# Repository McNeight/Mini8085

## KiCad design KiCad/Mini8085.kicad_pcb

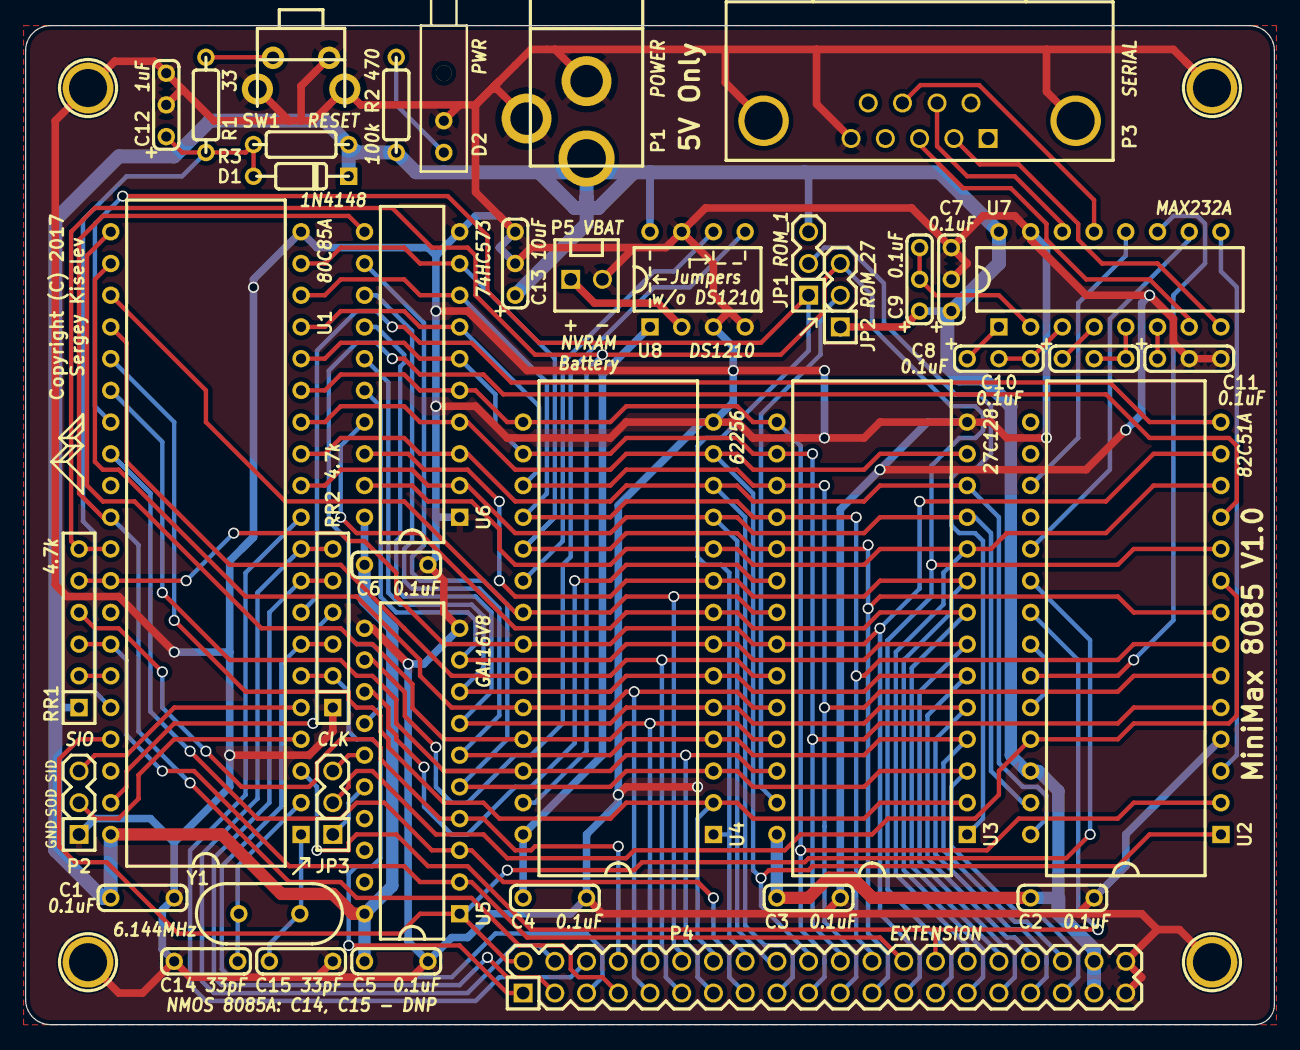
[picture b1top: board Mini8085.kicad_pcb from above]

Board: 2 copper layers, 100.0 x 80.0 mm, 44 parts (0 on the bottom side), 74 nets.

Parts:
C1, C2, C3, C4, C5, C6: 0.1uF; Cap_Cer_508
C7, C8, C9, C10, C11: 0.1uF; Cap_Pol_508_3
C12: 1uF; Cap_Pol_508_3
C13: 10uF; Cap_Pol_508_3
C14, C15: 33pF; Cap_Cer_508
D1: 1N4148; Diode_762
D2: PWR; LED_Dialight_566-0206F
HOLE1, HOLE2, HOLE3, HOLE4: CONN_1; Hole_3mm
JP1: ROM_1; Conn_Pin_Header_3x1_2.54mm
JP2: ROM_27; Conn_Pin_Header_3x1_2.54mm
JP3: CLK; Conn_Pin_Header_3x1_2.54mm
P1: POWER; Conn_Power_Jack_Circular_Pads
P2: SIO; Conn_Pin_Header_3x1_2.54mm
P3: SERIAL; Conn_Dsub_DE9M
P4: EXTENSION; Conn_Pin_Header_20x2_2.54mm
P5: VBAT; Conn_Friction_Lock_2P_2.54mm
R1: 33; Res_762
R2: 470; Res_762
R3: 100k; Res_762
RR1, RR2: 4.7k; Conn_SIL6
SW1: RESET; Switch_Tactile_6mm_Right
U1: 80C85A; IC_DIP40_600
U2: 82C51A; IC_DIP28_600
U3: 27C128; IC_DIP28_600
U4: 62256; IC_DIP28_600
U5: GAL16V8; IC_DIP20_300
U6: 74HC573; IC_DIP20_300
U7: MAX232A; IC_DIP16_300
U8: DS1210; IC_DIP8_300
Y1: 6.144MHz; Crystal_HC-49U_Vert

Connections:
/3.072MHz: P4.2, U1.37 (CLK), U2.20 (CLK), U5.1 (I/CLK)
/153.6kHz: JP3.3, U5.15 (I/O5)
/307.2kHz: JP3.1, U5.16 (I/O4)
/A0: P4.30, U2.12 (C/~D), U3.10 (A0), U4.10 (A0), U6.19 (O0)
/A1: P4.29, U3.9 (A1), U4.9 (A1), U6.18 (O1)
/A2: P4.32, U3.8 (A2), U4.8 (A2), U6.17 (O2)
/A3: P4.31, U3.7 (A3), U4.7 (A3), U5.9 (I8), U6.16 (O3)
/A4: P4.34, U3.6 (A4), U4.6 (A4), U5.8 (I7), U6.15 (O4)
/A5: P4.33, U3.5 (A5), U4.5 (A5), U5.7 (I6), U6.14 (O5)
/A6: P4.36, U3.4 (A6), U4.4 (A6), U5.6 (I5), U6.13 (O6)
/A7: P4.35, U3.3 (A7), U4.3 (A7), U5.5 (I4), U6.12 (O7)
/A8: P4.10, U1.21 (A8), U3.25 (A8), U4.25 (A8)
/A9: P4.9, U1.22 (A9), U3.24 (A9), U4.24 (A9)
/A10: P4.12, U1.23 (A10), U3.21 (A10), U4.21 (A10)
/A11: P4.11, U1.24 (A11), U3.23 (A11), U4.23 (A11)
/A12: P4.14, U1.25 (A12), U3.2 (A12), U4.2 (A12)
/A13: P4.13, U1.26 (A13), U3.26 (A13), U4.26 (A13)
/A14: JP1.1, P4.16, U1.27 (A14), U4.1 (A14)
/A15: P4.15, U1.28 (A15), U5.3 (I2)
/AD0: P4.18, U1.12 (AD0), U2.27 (D0), U3.11 (DQ0), U4.11 (DQ0), U6.2 (D0)
/AD1: P4.17, U1.13 (AD1), U2.28 (D1), U3.12 (DQ1), U4.12 (DQ1), U6.3 (D1)
/AD2: P4.20, U1.14 (AD2), U2.1 (D2), U3.13 (DQ2), U4.13 (DQ2), U6.4 (D2)
/AD3: P4.19, U1.15 (AD3), U2.2 (D3), U3.15 (DQ3), U4.15 (DQ3), U6.5 (D3)
/AD4: P4.22, U1.16 (AD4), U2.5 (D4), U3.16 (DQ4), U4.16 (DQ4), U6.6 (D4)
/AD5: P4.21, U1.17 (AD5), U2.6 (D5), U3.17 (DQ5), U4.17 (DQ5), U6.7 (D5)
/AD6: P4.24, U1.18 (AD6), U2.7 (D6), U3.18 (DQ6), U4.18 (DQ6), U6.8 (D6)
/AD7: P4.23, U1.19 (AD7), U2.8 (D7), U3.19 (DQ7), U4.19 (DQ7), U6.9 (D7)
/ALE: P4.7, U1.30 (ALE), U6.11 (LE)
/CTS: P3.8, U7.13 (R1IN)
/HOLD: RR2.4, U1.39 (HOLD)
/INTR: P4.4, RR2.6, U1.10 (INTR)
/IO/~M: P4.26, RR1.3, U1.34 (IO/~M), U5.2 (I1)
/RAM_VCC: C4.1, U4.28 (VCC), U8.1 (VCCO)
/READY: RR1.2, U1.35 (READY)
/RESET: P4.28, U1.3 (RES_OUT), U2.21 (RESET)
/ROM_1: JP1.2, U3.1 (VPP)
/ROM_27: JP2.2, U3.27 (~PGM)
/RST5_5: P4.3, RR2.5, U1.9 (RST5_5)
/RST6_5: U1.8 (RST6_5), U2.14 (RXRDY)
/RST7_5: P4.5, RR2.3, U1.7 (RST7_5)
/RTS: P3.7, U7.14 (T1OUT)
/RX: P3.2, U7.8 (R2IN)
/RXD: U2.3 (RXD), U7.9 (R2OUT)
/SID: P2.3, U1.5 (SID)
/SOD: P2.2, U1.4 (SOD)
/TRAP: P4.1, RR2.2, U1.6 (TRAP)
/TX: P3.3, U7.7 (T2OUT)
/TXD: U2.19 (TXD), U7.10 (T2IN)
/UART_CLK: JP3.2, U2.9 (~TXC), U2.25 (~RXC)
/VBAT: P5.1, U8.2 (VBAT1)
/~CTS: U2.17 (~CTS), U7.12 (R1OUT)
/~INTA: P4.6, U1.11 (~INTA)
/~RAM_CSO: U4.20 (~CE), U8.6 (~CEO)
/~RAM_CS: U5.12 (I/O8), U8.5 (~CE)
/~RD: P4.25, RR1.5, U1.32 (~RD), U2.13 (~RD), U3.22 (~OE), U4.22 (~OE)
/~ROM_CS: U3.20 (~CE), U5.13 (I/O7)
/~RTS: U2.23 (~RTS), U7.11 (T1IN)
/~SWAP_MEM: P4.8, RR1.4, U5.4 (I3)
/~USART_CS: U2.11 (~CS), U5.14 (I/O6)
/~WR: JP2.3, P4.27, RR1.6, U1.31 (~WR), U2.10 (~WR), U4.27 (~WE)
GND: C1.2, C2.2, C3.2, C4.2, C5.2, C6.2, C7.2, C11.2, C12.2, C13.2, C14.2, C15.2, D2.1 (K), HOLE1.1, HOLE2.1, HOLE3.1, HOLE4.1, P1.2, P1.3, P2.1, P3.5, P4.39, P4.40, P5.2, RR2.1 (COM), SW1.1, SW1.GND, U1.20 (GND), U2.4 (GND), U3.14 (GND), U4.14 (GND), U5.10 (GND), U5.11 (I9/~OE), U6.1 (~OE), U6.10 (GND), U7.15 (GND), U8.3 (TOL), U8.4 (GND), U8.7 (VBAT2)
unnamed: C8.1, U7.1 (C1+)
unnamed: C8.2, U7.3 (C1-)
unnamed: C9.2, U7.2 (V+)
unnamed: C10.1, U7.4 (C2+)
unnamed: C10.2, U7.5 (C2-)
unnamed: C11.1, U7.6 (V-)
unnamed: C12.1, D1.2 (A), R1.1, R3.2, U1.36 (~RES_IN)
unnamed: C14.1, U1.2 (X2), Y1.2
unnamed: C15.1, U1.1 (X1), Y1.1
unnamed: D2.2 (A), R2.1
unnamed: R1.2, SW1.2
unnamed: U2.22 (~DSR), U2.24 (~DTR)
VCC: C1.1, C2.1, C3.1, C5.1, C6.1, C7.1, C9.1, C13.1, D1.1 (K), JP1.3, JP2.1, P1.1, P4.37, P4.38, R2.2, R3.1, RR1.1 (COM), U1.40 (VCC), U2.26 (VCC), U3.28 (VCC), U5.20 (VCC), U6.20 (VCC), U7.16 (VCC), U8.8 (VCC)

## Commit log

2022-08-25 * Add Mini8085 - Board - 1.0.pdf * Update KiCad project to KiCad v6

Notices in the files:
KiCad/Mini8085.kicad_pcb:
Copyright (C) 2017
